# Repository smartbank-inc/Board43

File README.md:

# Board43

Board43 is an RP2350A-based microcontroller development board. Flash PicoRuby or your favorite firmware and start hacking.

## Directory Structure

| Directory                     | Description                                                                                                                                                                                  | License                                          |
| ----------------------------- | -------------------------------------------------------------------------------------------------------------------------------------------------------------------------------------------- | ------------------------------------------------ |
| [`docs/`](./docs)             | Reference manual and its compiler                                                                                                                                                            | MIT (compiler) / CC BY-SA 4.0 (document content) |
| [`firmware/`](./firmware)     | PicoRuby-based firmware                                                                                                                                                                      | MIT                                              |
| [`pcb/`](./pcb)               | KiCad PCB design data                                                                                                                                                                        | CERN-OHL-W-2.0 (some files under CC BY-SA 4.0)   |
| [`playground/`](./playground) | Browser-based PicoRuby IDE                                                                                                                                                                   | MIT                                              |
| [`workshop/`](./workshop)     | Workshop materials ([Japanese](https://github.com/smartbank-inc/Board43/blob/main/workshop/README.md) / [English](https://github.com/smartbank-inc/Board43/blob/main/workshop/README_en.md)) | CC BY-SA 4.0                                     |

## License

Each directory in this repository is licensed independently. See the `LICENSE` file or `README` in each directory for details.

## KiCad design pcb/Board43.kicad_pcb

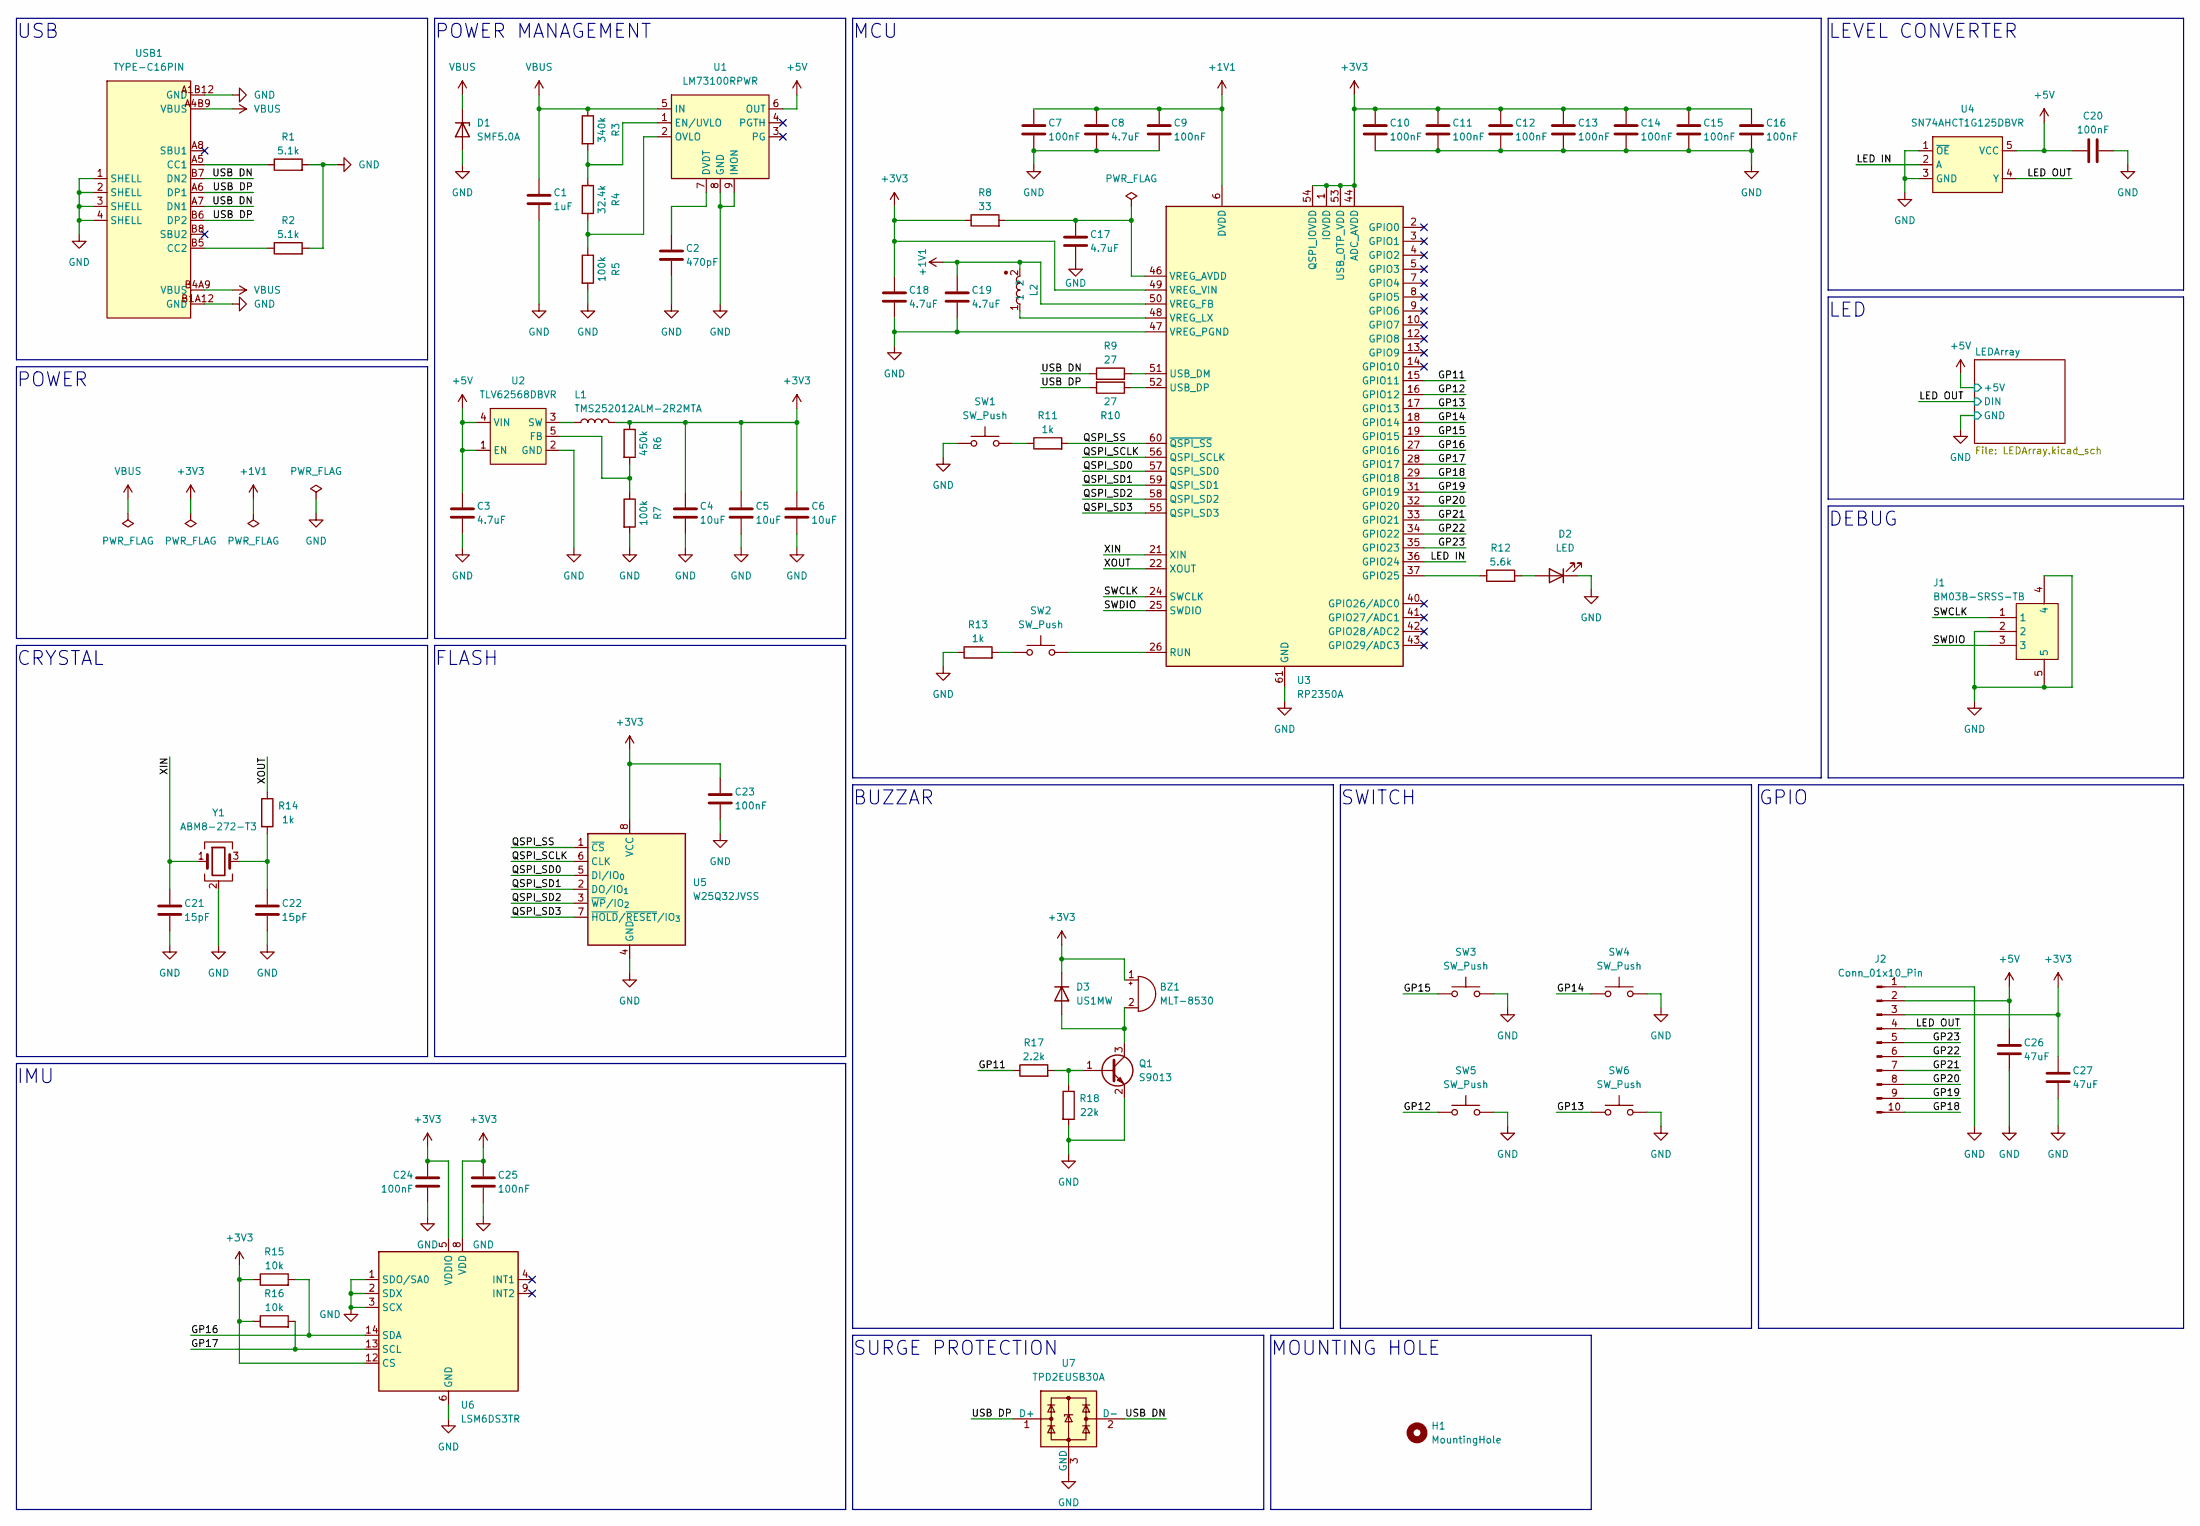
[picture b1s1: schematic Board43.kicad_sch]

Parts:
BZ1: MLT-8530; LCSC C94599
C1: 1uF; C_0402_1005Metric; LCSC C528974
C2: 470pF; C_0201_0603Metric; LCSC C384950
C3, C8, C17: 4.7uF; C_0402_1005Metric; LCSC C368809
C4, C5, C6: 10uF; C_0603_1608Metric; LCSC C2959727
C7, C9, C10, C11, C12, C13, C14, C15, C16: 100nF; C_0201_0603Metric; LCSC C668346
C18, C19: 4.7uF; C_0402_1005Metric_Narrow; LCSC C368809
C20, C23, C24, C25: 100nF; C_0402_1005Metric; LCSC C1525
C21, C22: 15pF; C_0402_1005Metric; LCSC C76950
C26, C27: 47uF; C_1206_3216Metric; LCSC C96123
D1: SMF5.0A; D_SOD-123F; LCSC C193402
D2: LED; KT-0603W; LCSC C2290
D3: US1MW; D_SOD-123F; LCSC C116132
H1: MountingHole; MountingHole_3.2mm_M3
J1: BM03B-SRSS-TB; LCSC C160389
J2: Conn_01x10_Pin; PinHeader_1x10_P2.54mm_Vertical
L1: TMS252012ALM-2R2MTA; L_1008_2520Metric; LCSC C1017131
L2: L; AOTA-B201610S3R3-101-T; LCSC C42411119
Q1: S9013; SOT-23; LCSC C727139
R1, R2: 5.1k; R_0201_0603Metric; LCSC C270344
R3: 340k; R_0402_1005Metric; LCSC C423187
R4: 32.4k; R_0402_1005Metric; LCSC C26974
R5, R7: 100k; R_0402_1005Metric; LCSC C25741
R6: 450k; R_0402_1005Metric; LCSC C5159688
R8: 33; R_0402_1005Metric; LCSC C25105
R9, R10: 27; R_0201_0603Metric; LCSC C473051
R11, R13, R14: 1k; R_0201_0603Metric; LCSC C270365
R12: 5.6k; R_0201_0603Metric; LCSC C423481
R15, R16: 10k; R_0201_0603Metric; LCSC C270334
R17: 2.2k; R_0402_1005Metric; LCSC C25879
R18: 22k; R_0402_1005Metric; LCSC C25768
SW1, SW2, SW3, SW4, SW5, SW6: SW_Push; SKRPACE010; LCSC C139797
U1: LM73100RPWR; LCSC C3210761
U2: TLV62568DBVR; SOT-23-5; LCSC C163219
U3: RP2350A; LCSC C42411118
U4: SN74AHCT1G125DBVR; SOT-23-5; LCSC C7484
U5: W25Q32JVSS; SOIC-8_5.3x5.3mm_P1.27mm; LCSC C82344
U6: LSM6DS3TR; LGA-14_3x2.5mm_P0.5mm_LayoutBorder3x4y; LCSC C95230
U7: TPD2EUSB30A; TPD2EUSB30ADRTR; LCSC C94934
USB1: TYPE-C16PIN; LCSC C393939
Y1: ABM8-272-T3; Crystal_SMD_3225-4Pin_3.2x2.5mm; LCSC C20625731

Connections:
+1V1: C7.1, C8.1, C9.1, C19.1, L2.2, U3.6 (DVDD), U3.23 (DVDD), U3.39 (DVDD), U3.50 (VREG_FB)
+3V3: BZ1.1 (+), C4.1, C5.1, C6.1, C10.1, C11.1, C12.1, C13.1, C14.1, C15.1, C16.1, C18.1, C23.1, C24.2, C25.1, C27.1, D3.1 (K), J2.3, L1.2, R6.1, R8.1, R15.1, R16.1, U3.1 (IOVDD), U3.11 (IOVDD), U3.20 (IOVDD), U3.30 (IOVDD), U3.38 (IOVDD), U3.44 (ADC_AVDD), U3.45 (IOVDD), U3.49 (VREG_VIN), U3.53 (USB_OTP_VDD), U3.54 (QSPI_IOVDD), U5.8 (VCC), U6.5 (VDDIO), U6.8 (VDD), U6.12 (CS)
+5V: C3.1, C20.1, C26.1, J2.2, U1.6 (OUT), U2.1 (EN), U2.4 (VIN), U4.5 (VCC); also elsewhere on the board
/GP11: R17.1, U3.15 (GPIO11)
/GP12: SW5.1, U3.16 (GPIO12)
/GP13: SW6.1, U3.17 (GPIO13)
/GP14: SW4.1, U3.18 (GPIO14)
/GP15: SW3.1, U3.19 (GPIO15)
/GP16: R15.2, U3.27 (GPIO16), U6.14 (SDA)
/GP17: R16.2, U3.28 (GPIO17), U6.13 (SCL)
/GP18: J2.10, U3.29 (GPIO18)
/GP19: J2.9, U3.31 (GPIO19)
/GP20: J2.8, U3.32 (GPIO20)
/GP21: J2.7, U3.33 (GPIO21)
/GP22: J2.6, U3.34 (GPIO22)
/GP23: J2.5, U3.35 (GPIO23)
/LED IN: U3.36 (GPIO24), U4.2 (A)
/LED OUT: J2.4, U4.4 (Y); also elsewhere on the board
/QSPI_SCLK: U3.56 (QSPI_SCLK), U5.6 (CLK)
/QSPI_SD0: U3.57 (QSPI_SD0), U5.5 (DI/IO_{0})
/QSPI_SD1: U3.59 (QSPI_SD1), U5.2 (DO/IO_{1})
/QSPI_SD2: U3.58 (QSPI_SD2), U5.3 (~WP/IO_{2})
/QSPI_SD3: U3.55 (QSPI_SD3), U5.7 (~HOLD/~RESET/IO_{3})
/QSPI_SS: R11.2, U3.60 (~QSPI_SS), U5.1 (~CS)
/SWCLK: J1.1, U3.24 (SWCLK)
/SWDIO: J1.3, U3.25 (SWDIO)
/USB DN: R9.1, U7.2 (D-), USB1.A7 (DN1), USB1.B7 (DN2)
/USB DP: R10.2, U7.1 (D+), USB1.A6 (DP1), USB1.B6 (DP2)
/XIN: C21.1, U3.21 (XIN), Y1.1
/XOUT: R14.1, U3.22 (XOUT)
GND: C1.2, C2.2, C3.2, C4.2, C5.2, C6.2, C7.2, C8.2, C9.2, C10.2, C11.2, C12.2, C13.2, C14.2, C15.2, C16.2, C17.2, C18.2, C19.2, C20.2, C21.2, C22.2, C23.2, C24.1, C25.2, C26.2, C27.2, D1.2 (A), D2.1 (K), J1.2, J1.4, J1.5, J2.1, Q1.2 (E), R1.2, R2.2, R5.2, R7.2, R13.1, R18.2, SW1.1, SW3.2, SW4.2, SW5.2, SW6.2, U1.8 (GND), U1.9 (IMON), U2.2 (GND), U3.47 (VREG_PGND), U3.61 (GND), U4.1 (~OE), U4.3 (GND), U5.4 (GND), U6.1 (SDO/SA0), U6.2 (SDX), U6.3 (SCX), U6.6 (GND), U6.7 (GND), U7.3 (GND), USB1.1 (SHELL), USB1.2 (SHELL), USB1.3 (SHELL), USB1.4 (SHELL), USB1.A1B12 (GND), USB1.B1A12 (GND), Y1.2 (G), Y1.4 (G); also elsewhere on the board
unnamed: BZ1.2 (-), D3.2 (A), Q1.3 (C)
unnamed: C22.1, R14.2, Y1.3
unnamed: D2.2 (A), R12.2
unnamed: Q1.1 (B), R17.2, R18.1
unnamed: R11.1, SW1.2
unnamed: R13.2, SW2.1
unnamed: C2.1, U1.7 (DVDT)
unnamed: R3.2, R4.1, U1.1 (EN/UVLO)
unnamed: R4.2, R5.1, U1.2 (OVLO)
unnamed: R6.2, R7.1, U2.5 (FB)
unnamed: L1.1, U2.3 (SW)
unnamed: R12.1, U3.37 (GPIO25)
unnamed: SW2.2, U3.26 (RUN)
unnamed: R9.2, U3.51 (USB_DM)
unnamed: R10.1, U3.52 (USB_DP)
unnamed: C17.1, R8.2, U3.46 (VREG_AVDD)
unnamed: L2.1, U3.48 (VREG_LX)
unnamed: R1.1, USB1.A5 (CC1)
unnamed: R2.1, USB1.B5 (CC2)
VBUS: C1.1, D1.1 (K), R3.1, U1.5 (IN), USB1.A4B9 (VBUS), USB1.B4A9 (VBUS)

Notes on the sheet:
GPIO
MOUNTING HOLE
SWITCH
USB
SURGE PROTECTION
FLASH
LED
DEBUG
MCU
IMU
LEVEL CONVERTER
CRYSTAL
POWER
BUZZAR
POWER MANAGEMENT
